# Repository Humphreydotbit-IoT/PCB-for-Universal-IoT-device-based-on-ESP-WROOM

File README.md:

# PCB-for-Universal-IoT-device-based-on-ESP-WROOM

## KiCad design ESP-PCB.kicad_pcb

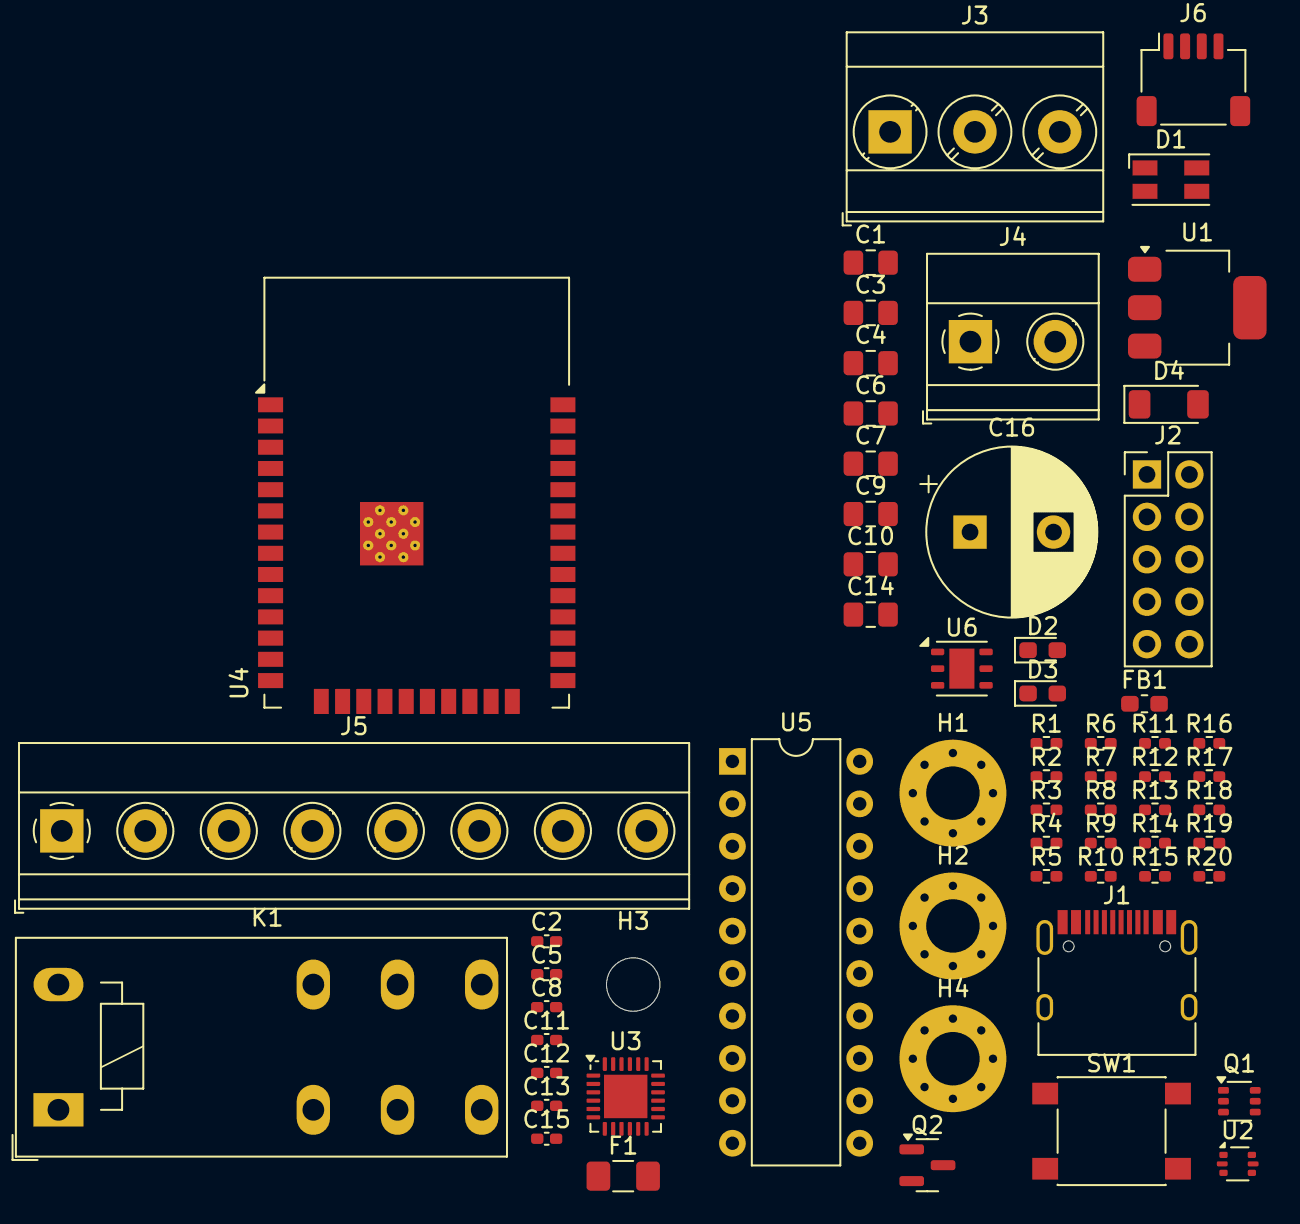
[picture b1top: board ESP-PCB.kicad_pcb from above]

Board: 2 copper layers, 62 parts (0 on the bottom side), 28 nets, no tracks yet.

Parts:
C1, C3, C4, C9, C10, C14: 22u; C_0805_2012Metric_Pad1.18x1.45mm_HandSolder
C2, C5, C8, C11, C12, C13, C15: 100n; C_0402_1005Metric_Pad0.74x0.62mm_HandSolder
C6, C7: 4u7; C_0805_2012Metric_Pad1.18x1.45mm_HandSolder
C16: 1000u/25V; CP_Radial_D10.0mm_P5.00mm
D1: LED_RGBA; LED_RGB_Wuerth-PLCC4_3.2x2.8mm_150141M173100
D2: GREEN; LED_0603_1608Metric_Pad1.05x0.95mm_HandSolder
D3: YELLOW; LED_0603_1608Metric_Pad1.05x0.95mm_HandSolder
D4: LL4148; D_MiniMELF
F1: Polyfuse 1A; Fuse_1206_3216Metric_Pad1.42x1.75mm_HandSolder
FB1: BLM21PG221; L_0603_1608Metric_Pad1.05x0.95mm_HandSolder
H1, H2, H4: Hole_Pad; MountingHole_3.2mm_M3_Pad_Via
H3: Hole_Pad; MountingHole_3.2mm_M3_DIN965
J1: USB_C_Receptacle_USB2.0; USB_C_Receptacle_HRO_TYPE-C-31-M-12
J2: Conn_02x05_Odd_Even; PinHeader_2x05_P2.54mm_Vertical
J3: Screw_Terminal_01x03; TerminalBlock_Phoenix_MKDS-3-3-5.08_1x03_P5.08mm_Horizontal
J4: Screw_Terminal_01x02; TerminalBlock_Phoenix_MKDS-1,5-2-5.08_1x02_P5.08mm_Horizont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
J5: Screw_Terminal_01x08; TerminalBlock_Phoenix_MKDS-1,5-8_1x08_P5.00mm_Horizontal
J6: Conn_01x04; JST_SH_SM04B-SRSS-TB_1x04-1MP_P1.00mm_Horizontal
K1: RT314A05; Relay_SPDT_Schrack-RT1-16A-FormC_RM5mm
Q1: UMH3N; SOT-363_SC-70-6
Q2: BC817; SOT-23
R1, R8, R9, R16: 10K; R_0402_1005Metric_Pad0.72x0.64mm_HandSolder
R2, R3: 5K1; R_0402_1005Metric_Pad0.72x0.64mm_HandSolder
R4, R5, R6, R7, R12, R14: 1K; R_0402_1005Metric_Pad0.72x0.64mm_HandSolder
R10, R11, R17, R18, R19, R20: 22R; R_0402_1005Metric_Pad0.72x0.64mm_HandSolder
R13, R15: 4K7; R_0402_1005Metric_Pad0.72x0.64mm_HandSolder
SW1: SW_SPST; SW_Push_1P1T_NO_6x6mm_H9.5mm
U1: TLV1117LV-3.3; SOT-223-3_TabPin2
U2: USBLC6-2P6; SOT-666
U3: CP2104; QFN-24-1EP_4x4mm_P0.5mm_EP2.6x2.6mm
U4: ESP32-WROOM-32D
U5: 74AHCT245; DIP-20_W7.62mm
U6: Si7021-A20; DFN-6-1EP_3x3mm_P1mm_EP1.5x2.4mm

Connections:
+3.3V: C3.1, C9.1, C11.1, C14.1, C15.1, D1.4 (A), J2.1, J2.2, J6.2, R1.1, R7.1, R9.1, R13.1, R15.1, U1.2 (VO), U4.2 (VDD), U6.5 (VDD)
+3.3VA: C10.1, C12.1, R8.1, U3.5 (VIO), U3.6 (VDD)
+5V: C1.1, C4.1, C5.1, C6.1, C13.1, D4.1 (K), F1.2, K1.A1, R12.1, U1.3 (VI), U2.5 (VBUS), U3.7 (REGIN), U3.8 (VBUS), U5.1 (A->B), U5.20 (VCC)
+5VP: FB1.1, J1.A4 (VBUS), J1.A9 (VBUS), J1.B4 (VBUS), J1.B9 (VBUS)
/DTR: Q1.1 (E1), Q1.5 (B2), U3.23 (~DTR)
/EN: C8.1, Q1.3 (C2), R9.2, U4.3 (EN)
/GPIO26: J2.3, U4.11 (IO26)
/GPIO27: J2.5, U4.12 (IO27)
/GPIO32: J2.7, U4.8 (IO32)
/GPIO33: J2.4, U4.9 (IO33)
/GPIO34: J2.6, U4.6 (IO34)
/GPIO35: J2.8, U4.7 (IO35)
/IO0: Q1.6 (C1), U4.25 (IO0)
/LEDSTR1: U4.27 (IO16), U5.2 (A0)
/LEDSTR2: U4.28 (IO17), U5.3 (A1)
/LEDSTR3: U4.30 (IO18), U5.4 (A2)
/LEDSTR4: U4.31 (IO19), U5.5 (A3)
/LED_B: R6.1, U4.13 (IO14)
/LED_G: R5.1, U4.23 (IO15)
/LED_R: R4.1, U4.16 (IO13)
/RELAY: R14.1, U4.10 (IO25)
/RTS: Q1.2 (B1), Q1.4 (E2), U3.19 (~RTS)
/RX: R10.2, U4.34 (RXD0/IO3)
/SCL: J6.4, R15.2, U4.37 (IO23), U6.6 (SCL)
/SDA: J6.3, R13.2, U4.36 (IO22), U6.1 (SDA)
/SW: C2.1, R1.2, SW1.2 (B), U4.33 (IO21)
/TX: R11.2, U4.35 (TXD0/IO1)
GND: C1.2, C2.2, C3.2, C4.2, C5.2, C6.2, C7.2, C8.2, C9.2, C10.2, C11.2, C12.2, C13.2, C14.2, C15.2, C16.2, D2.1 (K), H1.1, H2.1, H4.1, J1.A1 (GND), J1.A12 (GND), J1.B1 (GND), J1.B12 (GND), J1.S1 (SHIELD), J2.9, J2.10, J4.2, J5.7, J5.8, J6.1, Q2.2 (E), R2.2, R3.2, R16.2, SW1.1 (A), U1.1 (GND), U2.2 (GND), U3.2 (GND), U3.25 (GND), U4.1 (GND), U4.15 (GND), U4.38 (GND), U4.39 (GND), U5.6 (A4), U5.7 (A5), U5.8 (A6), U5.9 (A7), U5.10 (GND), U5.19 (CE), U6.2 (GND), U6.7 (PAD)
